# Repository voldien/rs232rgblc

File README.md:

# RS232RGBLEDController #
-----

The *RS232RGBLEDController* is extension PCB board for motherboard. Where its connected via the *com port* and the 12V rail. Where a LED strip can be either connected via the RGB headers or the 12V+, GND and data pin. Where it RGB has dedicated pin for RGB and GND. Whereas the other one uses SPI to communicated with LED strip. 

Remark that the schematic and PCB layout and the software driver are still work in progress and has yet not been tested!

## Motivation ##
----
The project was created in order to take advantages of the *com port* commonly found on motherboard, which is seldom used by the majority of desktop user.

The board is intended to add support for a cheap alternative for RGB lightning for desktop computers.

## Installation ##
------
The following section covers how the install the driver on the destkop in order to communicate with the extension board from *userspace*. Where the library for interfacing with the board will be installed along with a command line program, which can alter the behavior of the board in runtime.

## Unix ##
The driver for *UNIX* system can be installed as followed:
```
make 
make install
```

## Examples ##
-----

## License ##
---
The source code for this project is licensed under the GPL+3 License - see the [LICENSE](LICENSE) file for details.
The hardware design for this project is under the OSHW License - See  for more detials.

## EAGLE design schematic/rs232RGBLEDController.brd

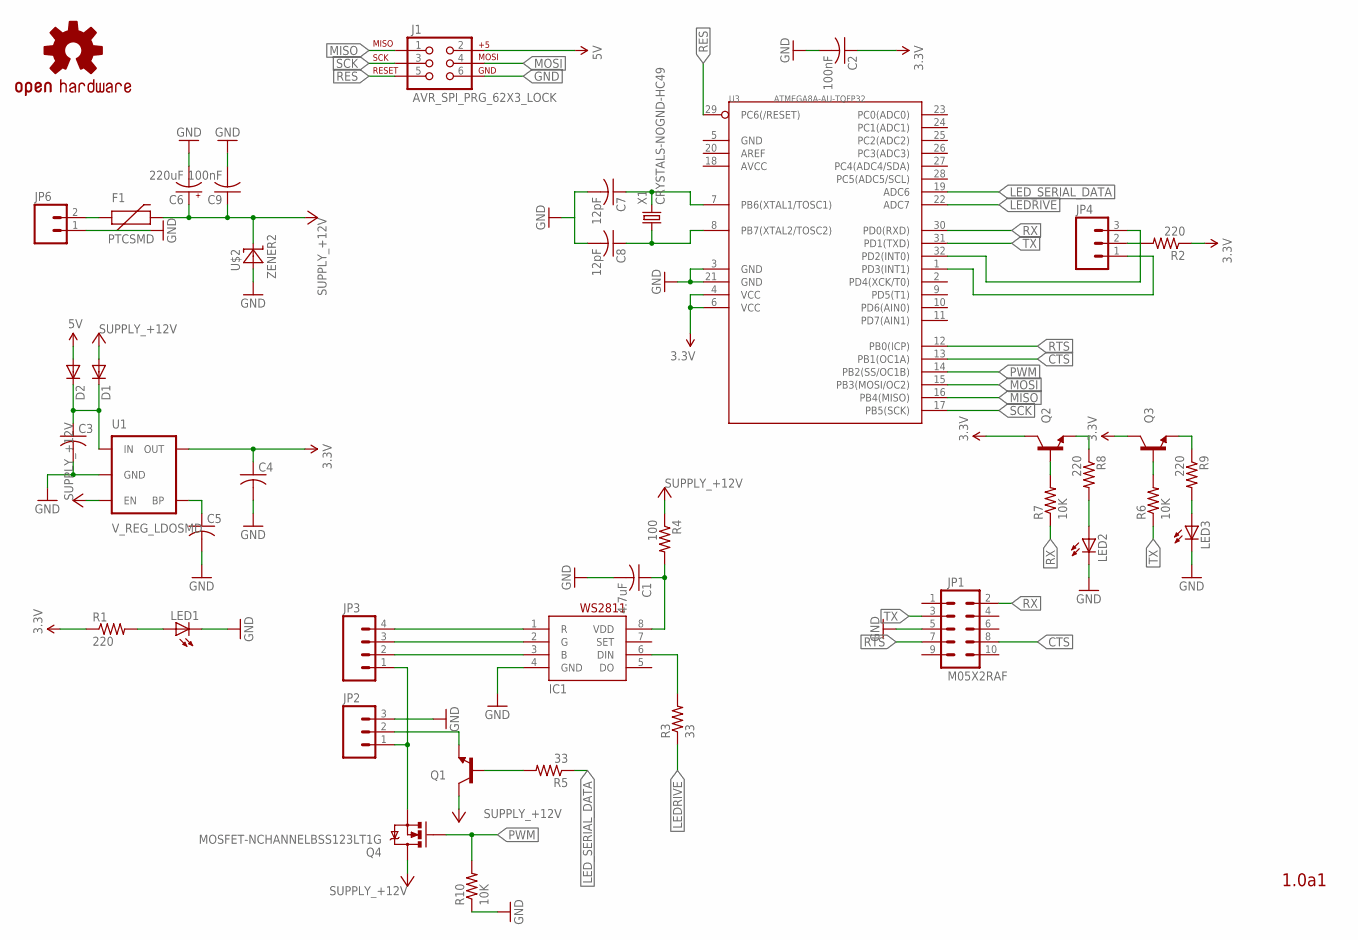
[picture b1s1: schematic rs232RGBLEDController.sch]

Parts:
C1: 4.7uF; C0603
C2, C9: 100nF; C0603
C3, C4, C5: C-USC0603; C0603
C6: 220uF; 175TMP-0810
C7, C8: 12pF; C0603
D1, D2: DIODESOT23; SOT23-3
F1: PTCSMD; PTC-1206
IC1: WS2811-SOP8; SO08-SKINNYPADS
J1: AVR_SPI_PRG_62X3_LOCK; 2X3_LOCK
JP1: M05X2RAF; 2X5-RAF
JP2, JP4: M03PTH; 1X03
JP3: M04PTH; 1X04
JP6: M021X02_NO_SILK; 1X02_NO_SILK
LED1, LED2, LED3: LED0603; LED-0603
Q1, Q2, Q3: TRANSISTOR_NPNSOT23; SOT23
Q4: MOSFET-NCHANNELBSS123LT1G; SOT23-3
R1, R2, R8, R9: 220; R0603
R3, R5: 33; R0603
R4: 100; R0603
R6, R7, R10: 10K; R0603
U1: V_REG_LDOSMD; SOT23-5
U3: ATMEGA8A-AU-TQFP32; TQFP32-0.8-7X7MM
U$1: OSHW-LOGOS; OSHW-LOGO-S
U$2: ZENER2; SOD123
X1: CRYSTALS-NOGND-HC49; HC49

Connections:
3.3V: C2.1, C4.1, Q2.3 (C), Q3.3 (C), R1.1, R2.1, U1.5 (OUT), U3.4 (VCC), U3.6 (VCC)
5V: D2.1 (A), J1.2
+12V: C6.+, C9.1, D1.1 (A), F1.2, Q1.3 (C), Q4.3 (D), R4.1, U1.3 (EN), U$2.C
CTS: JP1.8, U3.13 (PB1(OC1A))
GND: C1.2, C2.2, C3.2, C4.2, C5.2, C6.-, C7.2, C8.2, C9.2, IC1.4 (GND), J1.6, JP1.5, JP2.3, JP6.1, LED1.C, LED2.C, LED3.C, R10.1, U1.2 (GND), U3.3 (GND), U3.21 (GND), U$2.A
LEDRIVE: R3.1, U3.22 (ADC7)
LED_SERIAL_DATA: R5.1, U3.19 (ADC6)
MISO: J1.1, U3.16 (PB4(MISO))
MOSI: J1.4, U3.15 (PB3(MOSI/OC2))
unnamed: Q2.1 (B), R7.2
unnamed: C3.1, D1.3 (C), D2.3 (C), U1.1 (IN)
unnamed: Q3.1 (B), R6.2
unnamed: Q2.2 (E), R8.1
unnamed: LED2.A, R8.2
unnamed: JP2.1, JP3.1, Q4.2 (S)
unnamed: Q3.2 (E), R9.1
unnamed: LED3.A, R9.2
unnamed: JP2.2, Q1.2 (E)
unnamed: LED1.A, R1.2
unnamed: IC1.3 (B), JP3.2
unnamed: C5.1, U1.4 (BP)
unnamed: C8.1, U3.8 (PB7(XTAL2/TOSC2)), X1.1
unnamed: C7.1, U3.7 (PB6(XTAL1/TOSC1)), X1.2
unnamed: JP4.2, R2.2
unnamed: JP4.1, U3.1 (PD3(INT1))
unnamed: JP4.3, U3.32 (PD2(INT0))
unnamed: IC1.2 (G), JP3.3
unnamed: IC1.1 (R), JP3.4
unnamed: IC1.6 (DIN), R3.2
unnamed: C1.1, IC1.8 (VDD), R4.2
unnamed: Q1.1 (B), R5.2
unnamed: F1.1, JP6.2
PWM: Q4.1 (G), R10.2, U3.14 (PB2(SS/OC1B))
RES: J1.5, U3.29 (PC6(/RESET))
RTS: JP1.7, U3.12 (PB0(ICP))
RX: JP1.2, R7.1, U3.30 (PD0(RXD))
SCK: J1.3, U3.17 (PB5(SCK))
TX: JP1.3, R6.1, U3.31 (PD1(TXD))

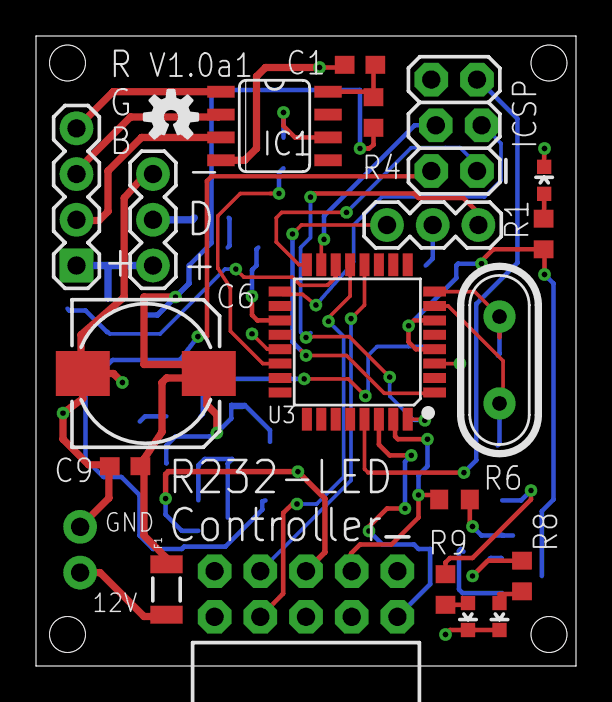
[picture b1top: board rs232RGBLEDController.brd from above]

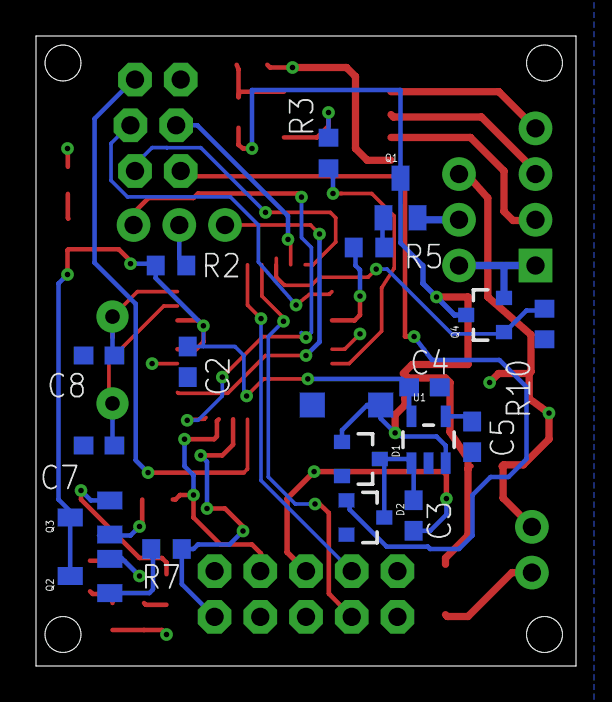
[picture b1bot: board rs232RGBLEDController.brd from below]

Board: 2 copper layers, 30.0 x 35.0 mm, 41 parts (19 on the bottom side), 38 nets.

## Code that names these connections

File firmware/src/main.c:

#include"r232lc.h"
#include"queue.h"
#include"uart.h"
#include"spi.h"
#include"anim.h"
#include"pwm.h"
#include"protocol.h"
#include<avr/wdt.h>

#include<avr/io.h>
#include<avr/interrupt.h>
#include<avr/fuse.h>
#include<avr/pgmspace.h>
#include<avr/sleep.h>
#include<stdio.h>
#include<avr/lock.h>
#include<avr/cpufunc.h>

/**
 *
 */
struct r232_led_state_t EEMEM ledstate = {0};

/**
 *
 */
const uint8_t PROGMEM statepin0 = PB6;
const uint8_t PROGMEM statepin1 = PB7;
const uint8_t PROGMEM sckpin = PB5;
const uint8_t PROGMEM mosipin = PB4;
const uint8_t PROGMEM misopin = PB3;
const uint8_t PROGMEM rxpin = PD0;
const uint8_t PROGMEM txpin = PD1;
const uint8_t PROGMEM ledserpin = PD2;
const uint8_t PROGMEM leddripin = PD3;
const uint8_t PROGMEM pwmpin = PB2;

/**
 *	Define global variable. It's recommended to
 *	set the queue size in power of two.
 */
volatile transmit_callback g_state_cb = NULL;
volatile struct queue_t rx_queue = {
	.size = 64,
};
volatile struct queue_t tx_queue = {
	.size = 16,
};
volatile struct queue_t led_queue = {
	.size = 32,
};
volatile struct animation_playback_t g_anim = {0};

volatile struct r232_state_t g_state = {
	.hstate = 0,
	.lstate = 0,
};


/*	TODO MOVE.	*/
void transmit_rgb_w2811(uint8_t r, uint8_t g, uint8_t b){
	spi_putchar(r);
	spi_putchar(g);
	spi_putchar(b);
}
void transmit_rgb_spidata(uint8_t r, uint8_t g, uint8_t b){
	spi_putchar(r);
	spi_putchar(g);
	spi_putchar(b);
}

/**
 *	Timer overflow.
 */
ISR(TIMER0_OVF_vect){

	/*	Check if SPI is ready.	*/
	if(spi_ready())
		return;

	/*	requires three bytes.	*/
	if(queue_size(&led_queue) < 3)
		return;

	uint8_t r,g,b;

	if(g_state.lstate & STATE_ANIM){
		/*	Load RGB from animation playback.	*/
		animation_get_next_rgb(&g_anim, &r, &g, &b);
	}else{
		/*	Load RGB from LED data queue.	*/
		r = queue_dequ(&led_queue);
		g = queue_dequ(&led_queue);
		b = queue_dequ(&led_queue);
	}

	/*	transmit.	*/
	g_state_cb(r,g,b);
}

/**
 *
 */
ISR(SPI_STC_vect){
	uint8_t de = queue_dequ(&led_queue);
	spi_directwrite(de);
}

ISR(USART_TXC_vect){
	/*	*/
	if(!queue_empty(&tx_queue)){
		uart_putchar( queue_dequ(&tx_queue) );
	}
}
ISR(USART_RXC_vect){

	/*	Recv next byte.	*/
	queue_enqu(&rx_queue, uart_direct_getchar());
	sleep_disable();
}

ISR(USART_UDRE_vect){

}


ISR(INT0_vect){
	g_state.hstate = STATE_USEW2811;
	g_state_cb = transmit_rgb_w2811;
}

ISR(INT1_vect){
	g_state.hstate = STATE_LED_DATA;
	g_state_cb = transmit_rgb_spidata;
}

int main(void){

	/*	Disable global interrupt.	*/
	cli();

	/*	Disable Watchdog timer.	*/
	wdt_disable();

	/*	Enable UART.	*/
	uart_init();
	uart_enable_interrupt();
	PORTD |= (1 << rxpin) | (1 << txpin);
	DDRD |= (1 << rxpin) | (1 << txpin);

	/*	Enable SPI.	*/
	spi_init();
	spi_enable_interrupt();
	PORTB |= (1 << sckpin) | (1 << mosipin) | (1 << misopin);
	DDRB |= (1 << sckpin) | (1 << mosipin) | (1 << misopin);

	/*	initialize queue.	*/
	init_queue(&rx_queue);
	init_queue(&tx_queue);
	init_queue(&led_queue);

	/*	state.	*/
	PORTD |= (1 << statepin0) | (1 << statepin1);
	DDRD &= ~((1 << statepin0) | (1 << statepin1));
	if(PIND & ( 1 << statepin0) ||
			PIND & ( 1 << statepin1)){
		g_state_cb = transmit_rgb_spidata;
	}else{
		g_state_cb = transmit_rgb_w2811;
	}

	/*	Enable external interrupt.	*/
	MCUCR |= (1 << ISC00) | (1 << ISC01) | (1 << ISC10) | (1 << ISC11);
	GIFR |= (1 << INTF0) | (1 << INTF1);


	/*	Timer interrupt.	*/
	TCCR0 |= (0 << CS02) | (0 << CS01) | (1 << CS02);
	TIMSK |= (1 << TOIE0);

	/*	Create default animation.	*/
	animation_create(&g_anim, 0);

	/*	PWM.	*/
	pwm_enable();
	PORTB |= ( 1 << pwmpin);
	DDRB |= ( 1 << pwmpin);

	/*	LED drive.	*/
	PORTC = (1 << leddripin) | (1 << ledserpin);

	/*	Watchdog for preventing the device from getting stuck.	*/
	wdt_enable( ((1 << WDP2) | (1 << WDP1) | (1 << WDP0)) );

	/*	Enable global interrupt.	*/
	sei();

	/*	Main loop.	*/
	while(1){
		/*	Sleep intill needed.	*/
		set_sleep_mode(SLEEP_MODE_PWR_SAVE);
		sleep_cpu();

		/*	Process command from RX UART.	*/
		while(!queue_empty(&rx_queue)){
			uint8_t buf = queue_dequ(&rx_queue);
			uint8_t com = get_command(buf);
			call_command(com, buf);
		}
	}

	return 0;
}

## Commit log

2017-07-23 Added git ignore rules.
2017-07-23 Added software license.
2017-07-24 Added init schematic and boardlayout.
2017-07-31 Init firmware.
2017-08-02 Added additional git ignore rules.
2017-08-13 Started adding driver for UNIX platforms. The Code has yet not been tested.
2017-08-13 Added root makefile.
2017-08-13 Removed useless file.
2017-08-13 Added additional git ignore rule.
2017-09-04 Started writting the readme for the project.
2017-10-04 Added restrict qualifier.
2017-10-04 Added const qualifier.
2017-10-04 Added some doc comments.
2017-10-14 Minor improvements.
2017-10-28 Minor.
2017-10-28 Added force inline macros.
2017-10-28 Replaced inline with always inline macro.
2017-11-08 Fixed some via size and other minor changes.
2017-11-08 Relocated silk screen for the plus sign.
2017-11-08 Added ICSP label and relocated some other labels.
2017-11-08 Added additional ground path for the LED.
2017-11-08 Minor changes.

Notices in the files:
parts and their libraries:
SparkFun: Licensing: CC v3.0 Share-Alike You are welcome to use this library for commercial purposes.
SparkFun-DiscreteSemi: Licensing: Creative Commons ShareAlike 4.0 International - https://creativecommons.org/licenses/by-sa/4.0
